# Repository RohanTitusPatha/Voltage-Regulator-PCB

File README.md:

# PCB Design for 5V and 9V Voltage Regulator

Welcome to the repository for my PCB design project focused on creating a reliable voltage regulator circuit capable of delivering both 5V and 9V outputs. This project aims to provide a stable power supply solution for various electronic applications.

## Project Highlights:

- **Dual Output Capability**: The designed PCB supports dual voltage outputs - 5V and 9V, catering to the diverse requirements of electronic projects.

- **Efficient Voltage Regulation**: The voltage regulator circuit ensures a consistent and stable output, essential for powering sensitive electronic components.

- **Compact and Optimized Layout**: The PCB layout is thoughtfully designed to optimize space utilization while maintaining signal integrity and minimizing noise.

- **Component Selection**: Careful consideration has been given to the selection of high-quality components to ensure reliability and longevity of the voltage regulator circuit.

## Usage Instructions:

1. **Power Input**: Connect your power source to the designated input terminal, ensuring it aligns with the recommended voltage and current specifications.

2. **Output Terminals**: Utilize the labeled output terminals for obtaining regulated power at both 5V and 9V as per your project requirements.

3. **Integration with Projects**: Incorporate this PCB into your electronic projects to provide a stable power supply for various components.

Feel free to explore the repository, clone it for your own use, or contribute to its development. Your feedback and suggestions are highly appreciated!

If you find this project helpful or have any questions, please don't hesitate to open an issue or reach out. Happy tinkering! 🛠️

## Image of PCB Editor

## Image of Escheema

## Image of 3-d viewer

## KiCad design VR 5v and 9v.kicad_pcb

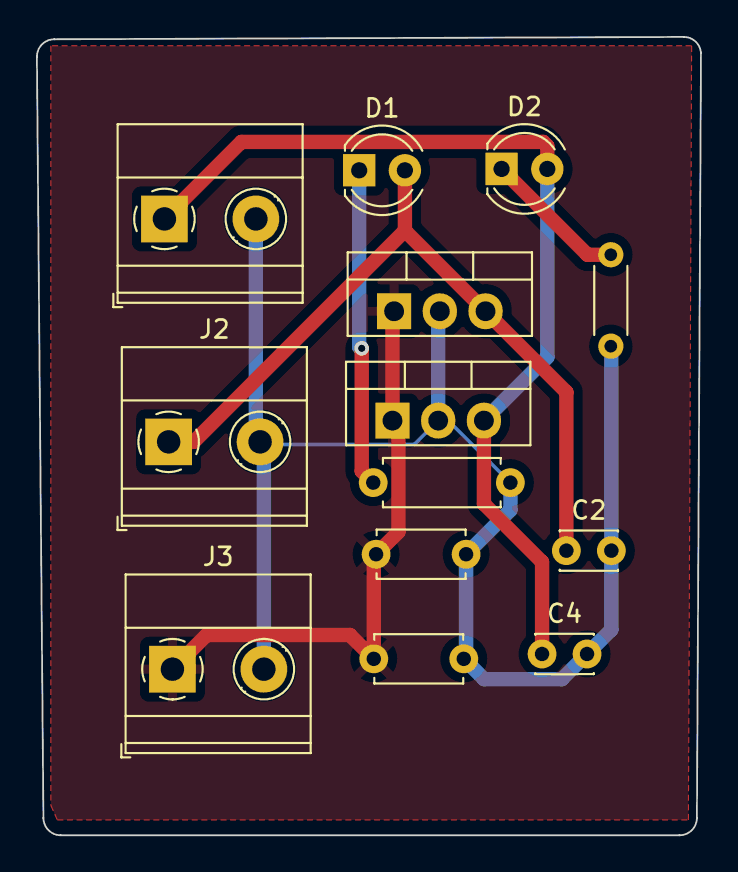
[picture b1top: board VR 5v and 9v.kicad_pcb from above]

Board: 2 copper layers, 36.9 x 44.4 mm, 7 parts (0 on the bottom side), 4 nets.

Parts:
C2: 0.1 uf; C_Disc_D3.0mm_W2.0mm_P2.50mm
C4: 0.1uf; C_Disc_D3.0mm_W2.0mm_P2.50mm
D1, D2: LED; LED_D4.0mm
J2: 9v; TerminalBlock_Phoenix_MKDS-1,5-2-5.08_1x02_P5.08mm_Horizont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
J3: 12v; TerminalBlock_Phoenix_MKDS-1,5-2-5.08_1x02_P5.08mm_Horizont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
R1: 1k ohm; R_Axial_DIN0207_L6.3mm_D2.5mm_P7.62mm_Horizontal

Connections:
5v: C4.1, D2.2 (A)
9v: C2.1, D1.2 (A), J2.1
GND: C2.2, C4.2, J2.2, J3.2, R1.2
unnamed: D1.1 (K), R1.1

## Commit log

2023-12-04 Add files via upload
    Escheema
2023-12-04 contains 3d images and report files
2023-12-04 contains Escheema nd pcb design
